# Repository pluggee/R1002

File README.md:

# R1002A
Quad 1A DC Low Side NFET Control Switches
License
-------
R1002A is released under the GNU GPL v3, which you can find at <http://www.gnu.org/licenses/gpl-3.0.en.html>,
Check License.md for more details.

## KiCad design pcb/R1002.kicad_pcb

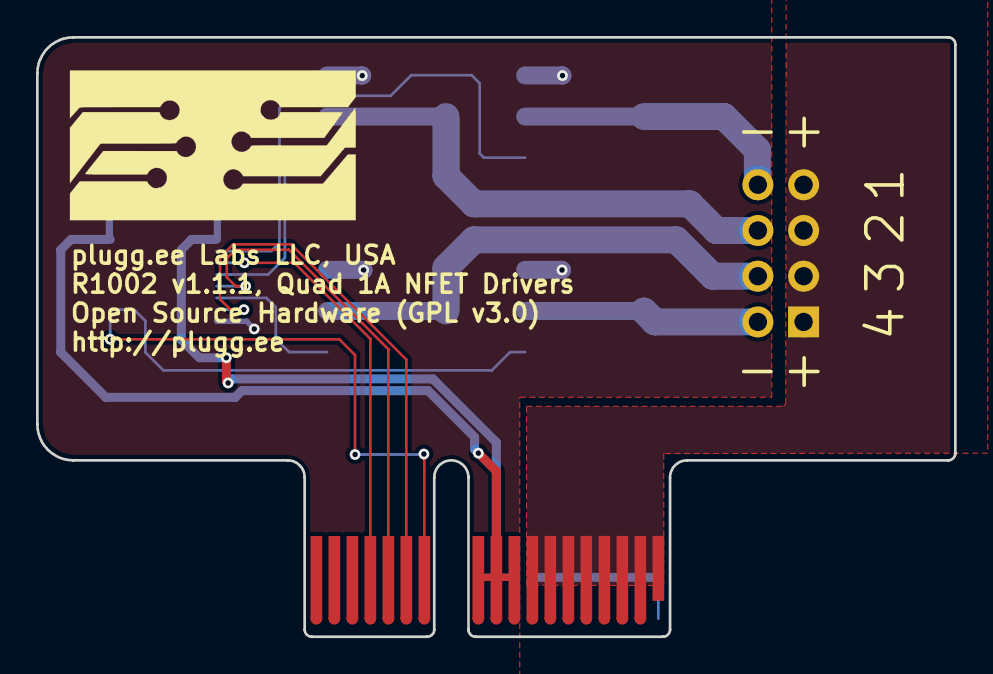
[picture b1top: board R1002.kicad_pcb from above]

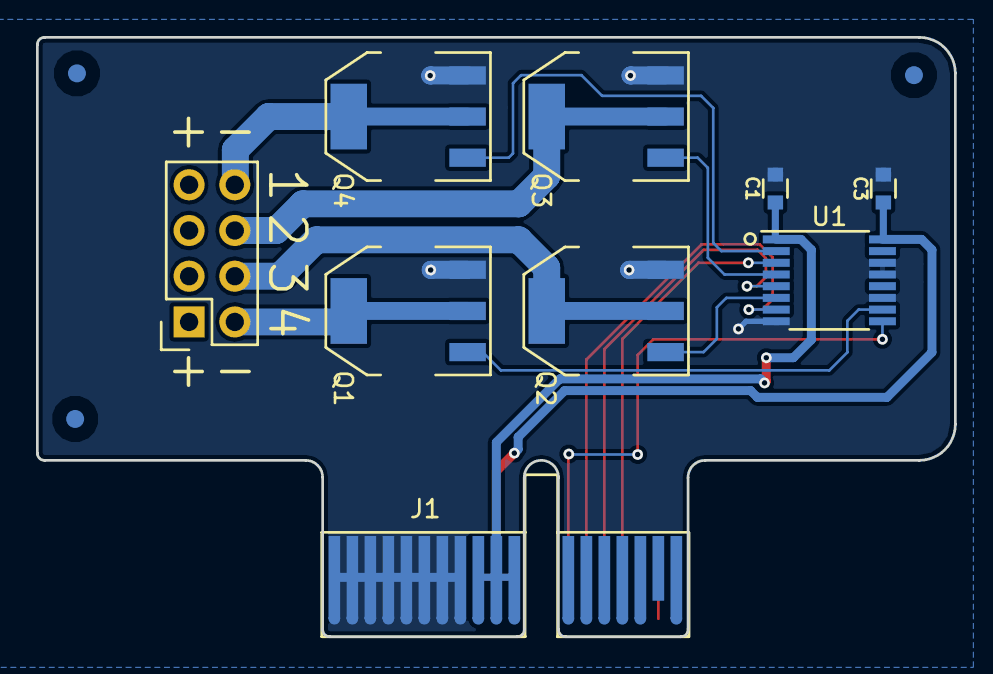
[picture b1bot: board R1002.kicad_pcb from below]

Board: 2 copper layers, 51.0 x 33.3 mm, 13 parts (12 on the bottom side), 16 nets.

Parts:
A1: ART; pluggeeLabsIcon-16X8
C1, C3: CC0603KRX7R9BB104; CAPC0603
FID1, FID2, FID3: FIDTOP001
J1: PCIEXPRESS-X1
J2: CONN254P-02X04
Q1, Q2, Q3, Q4: Q_NMOS_GDSD; SOT-223
U1: MC14504B-TSSOP; SOP65P500X440X120-16

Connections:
+3V3: C1.1, J1.B9, J1.B10, J1.B11, U1.1
+5V: C3.1, J1.A9, J1.A10, J1.A11, U1.16
/DN1: J2.8, Q4.2, Q4.4
/DN2: J2.6, Q3.2, Q3.4
/DN3: J2.4, Q2.2, Q2.4
/DN4: J2.2, Q1.2, Q1.4
/GN1: Q4.1, U1.2
/GN2: Q3.1, U1.4
/GN3: Q2.1, U1.6
/GN4: Q1.1, U1.10
GND: C1.2, C3.2, J1.B1, J1.B2, J1.B3, J1.B4, J1.B5, J1.B6, J1.B7, J1.B8, Q1.3, Q2.3, Q3.3, Q4.3, U1.8, U1.11, U1.13, U1.14
HT: J1.A1, J1.A2, J1.A3, J1.A4, J1.A5, J1.A6, J1.A7, J1.A8, J2.1, J2.3, J2.5, J2.7
PX1: J1.A12, U1.9
PX2: J1.A13, U1.7
PX3: J1.A14, U1.5
PX4: J1.A15, U1.3

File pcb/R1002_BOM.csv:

Reference;Quantity;Value;Footprint;Datasheet;Manufacturer;MPN;SKU;C;Tol;Vmax;Type
A1 ;1;ART;pluggee:pluggeeLabsIcon-16X8;
C1 C3 ;2;CC0603KRX7R9BB104;Main:CAPC0603;;Yageo;CC0603KRX7R9BB104;STUFF;100 nF;±10%;50.0V;X7R
FID1 FID2 FID3 ;3;FIDTOP001;Main:FIDTOP001;
J1 ;1;PCIEXPRESS-X1;Main:PCIEXPRESS-X1;;Amphenol FCI;10018784-10200TLF;;;;;
J2 ;1;CONN254P-02X04;Main:CONN254P-02X04;;Amphenol FCI;68021-408HLF;STUFF;;;;
Q1 Q2 Q3 Q4 ;4;Q_NMOS_GDSD;TO_SOT_Packages_SMD:SOT-223;;Diodes Inc;ZXMN4A06GTA;STUFF;;;;
U1 ;1;MC14504B-TSSOP;Main:SOP65P500X440X120-16;;ON Semiconductor;MC14504BDTR2G;SOFTPWM;;;;

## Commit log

2016-07-03 moved from R1000 repo
2016-07-08 refreshed QFN20 package
2016-07-23 releasing first beta
2016-08-19 added BOM
2017-02-02 added license clause
2017-03-24 cleaned up and renamed to R1002
2017-03-25 fixed R1002 layout, placed components on the correct side
2017-03-28 added fiducials, exported BOM
2017-03-28 fixed silk screen with v1.1
2017-03-29 added SMT assembly files
2017-04-16 getting ready to release
2017-04-16 narrowed PCB to avoid connector bump into PCB

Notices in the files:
pcb/R1002.kicad_pcb:
Open Source Hardware (GPL v3.0)
